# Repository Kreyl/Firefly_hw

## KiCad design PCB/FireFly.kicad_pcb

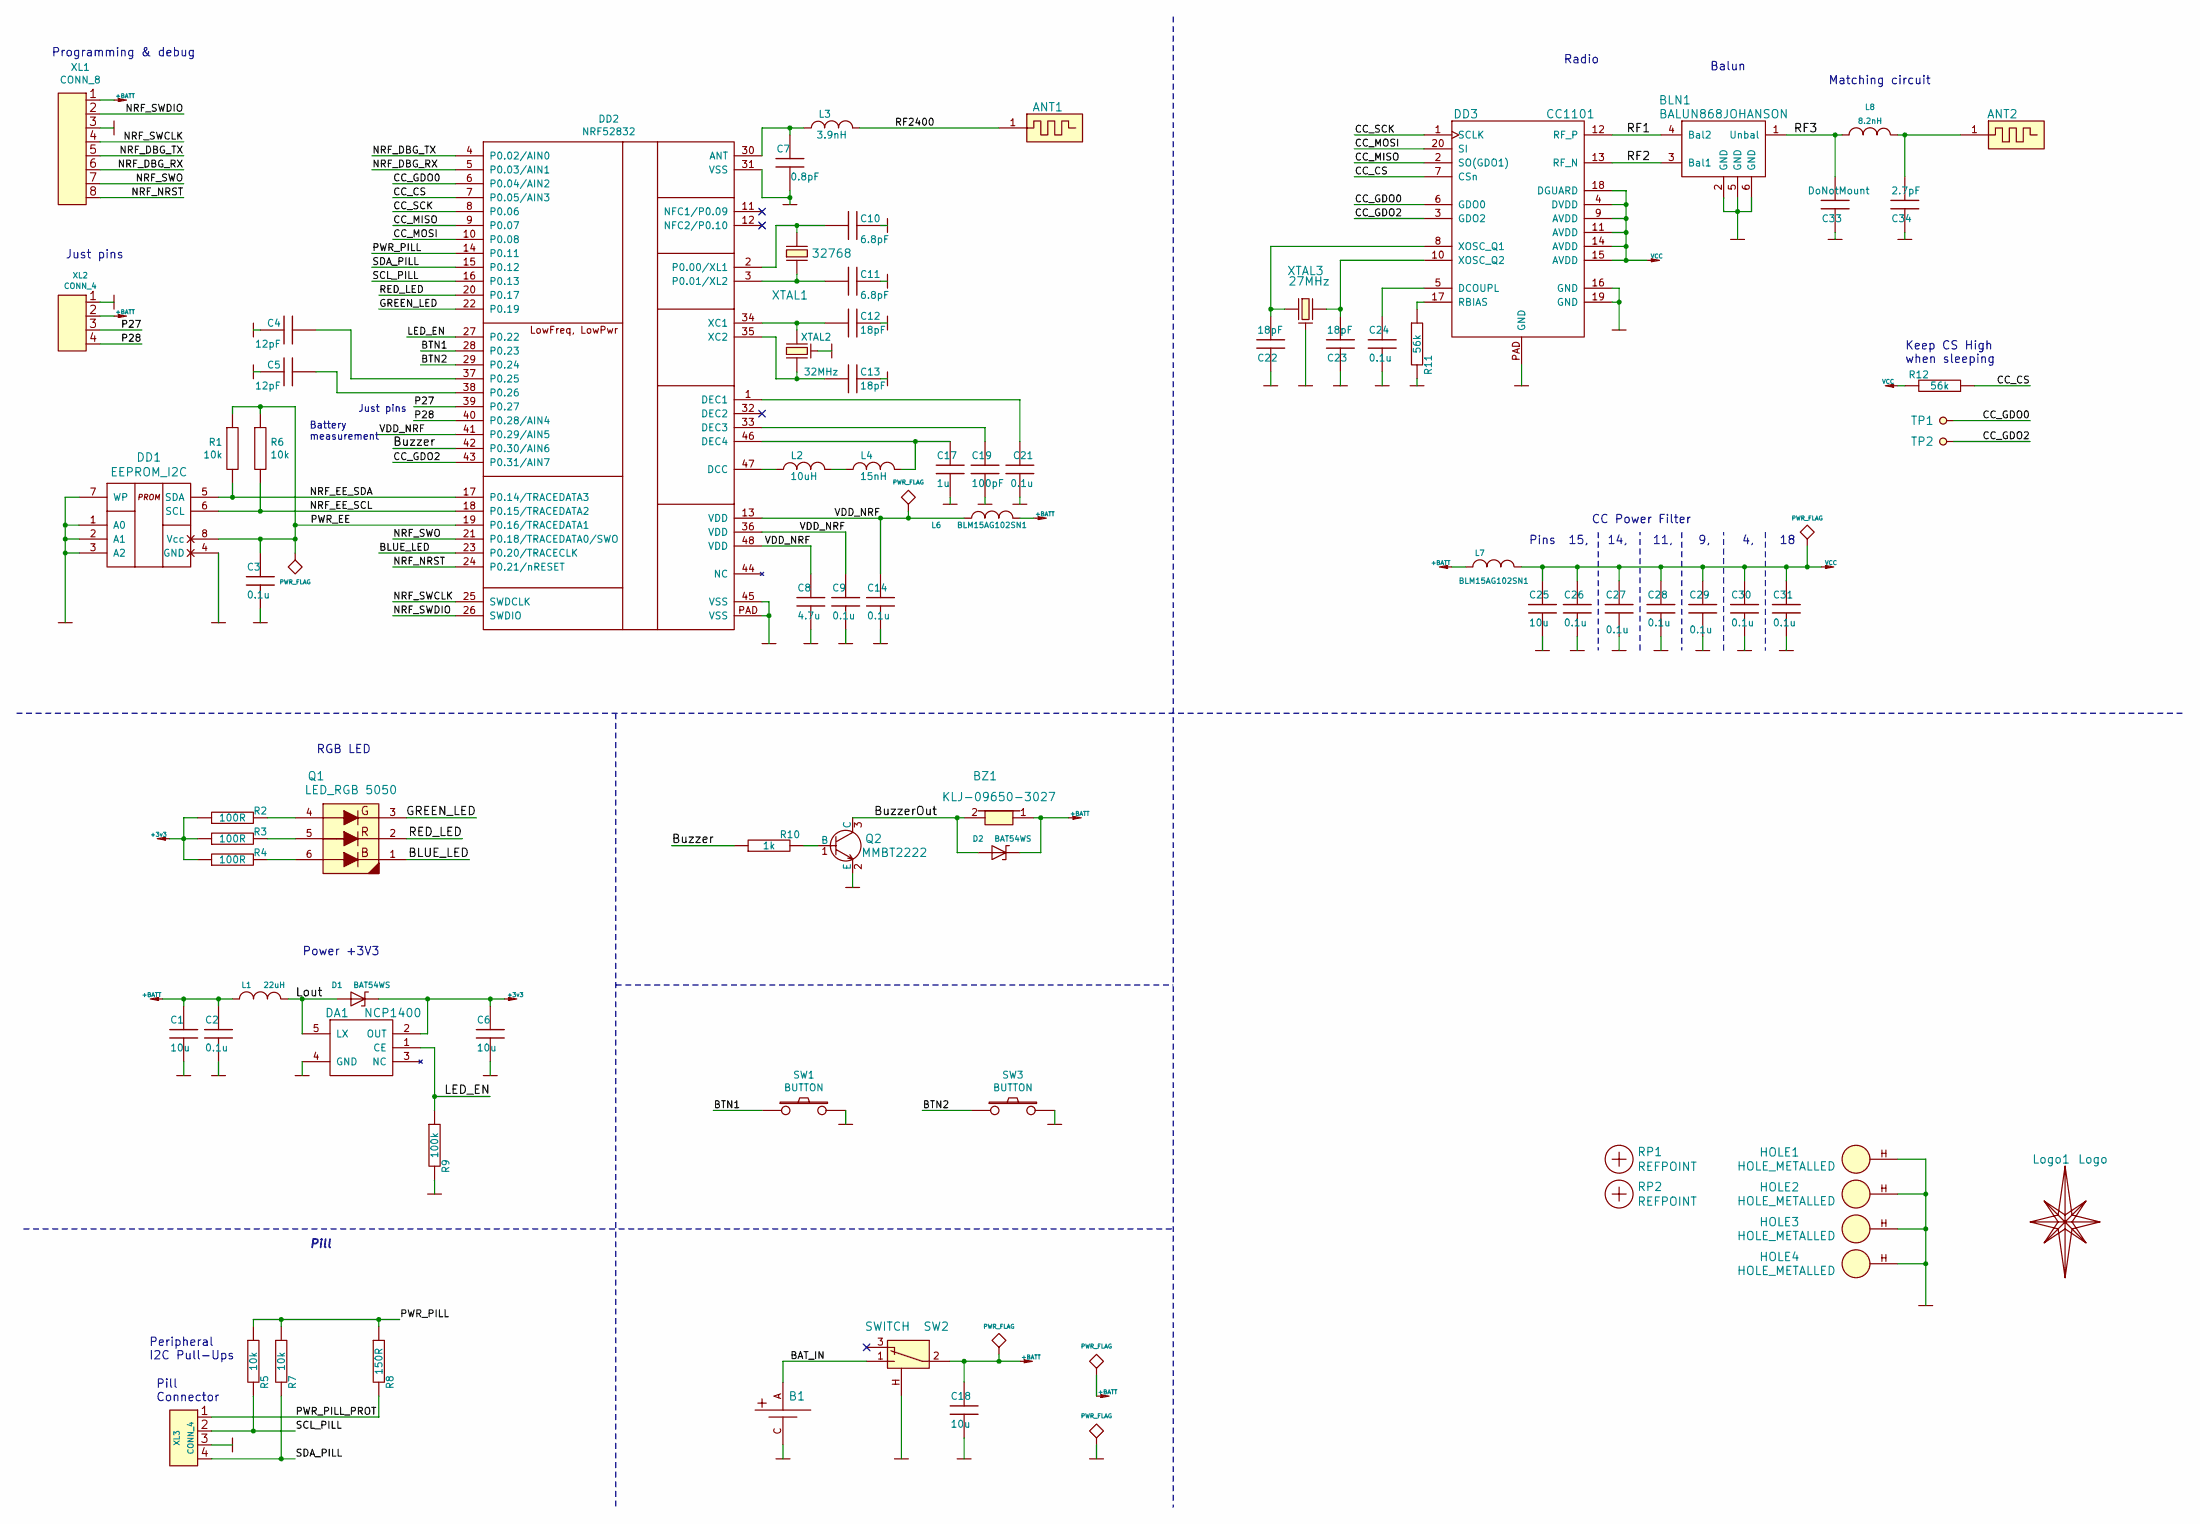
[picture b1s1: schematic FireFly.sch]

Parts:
ANT1: ANT_GENERAL; Firefly_2400
ANT2: ANT_PCB_MONO_2PIN; Firefly_868
B1: BAT_HOLDER; BATTERY_AAA_X2_PLUS_LEFT
BLN1: BALUN868JOHANSON; BALUN_JOHANSON868
BZ1: KLJ-09650-3027; BUZZER_KLJ-09650-3027
C1, C6, C18, C25: 10u; CAP_0603
C2, C3, C9, C14, C21, C24, C26, C27, C28, C29, C30, C31: 0.1u; CAP_0402
C4, C5: 12pF; CAP_0402
C7: 0.8pF; CAP_0402
C8: 4.7u; CAP_0603
C10, C11: 6.8pF; CAP_0402
C12, C13, C22, C23: 18pF; CAP_0402
C17: 1u; CAP_0402
C19: 100pF; CAP_0402
C33: DoNotMount; CAP_0402
C34: 2.7pF; CAP_0402
D1, D2: BAT54WS; SOD323
DA1: NCP1400; SOT23-5
DD1: EEPROM_I2C; SO8_150MIL
DD2: NRF52832; QFN-48_EP_6x6_Pitch0.4mm
DD3: CC1101; QFN20
HOLE1, HOLE2, HOLE3, HOLE4: HOLE_METALLED; Hole2d2_out3d5mm
L1: 22uH; IND_1210_LQH32C
L2: 10uH; IND_0603
L3: 3.9nH; IND_0402
L4: 15nH; IND_0402
L6, L7: BLM15AG102SN1; IND_0402
L8: 8.2nH; IND_0402
Logo1: Logo; Ostranna_12d7_10d1
Q1: LED_RGB 5050; LED_5050
Q2: MMBT2222; SOT23-3
R1, R5, R6, R7: 10k; RES_0603
R2, R3, R4: 100R; RES_0603
R8: 150R; RES_0603
R9: 100k; RES_0603
R10: 1k; RES_0603
R11, R12: 56k; RES_0603
RP1, RP2: REFPOINT; REF_POINT_1MM
SW1, SW3: BUTTON; BTN_4x4_SMD
SW2: SWITCH; SW_SS-1P2T_Housing
TP1, TP2: TESTPOINT; TESTPOINT_1MM
XL1: CONN_8; PLD-8_LOCK
XL2: CONN_4; PLS-4
XL3: CONN_4; PBS-4R
XTAL1: 32768; 03215C2
XTAL2: 32MHz; 03225C4
XTAL3: 27MHz; 03225C4

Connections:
+3v3: C6.2, D1.C, DA1.2 (OUT), R2.1, R3.1, R4.1
+BATT: BZ1.1, C1.2, C2.2, C18.2, D2.C, L1.2, L6.2, L7.2, SW2.2, XL1.1, XL2.2 (PM)
/BAT_IN: B1.A, SW2.1
/BLUE_LED: DD2.23 (P0.20/TRACECLK), Q1.1
/BTN1: DD2.28 (P0.23), SW1.1
/BTN2: DD2.29 (P0.24), SW3.1
/Buzzer: DD2.42 (P0.30/AIN6), R10.1
/BuzzerOut: BZ1.2, D2.A, Q2.3 (C)
/CC_CS: DD2.7 (P0.05/AIN3), DD3.7 (CSn), R12.1
/CC_GDO0: DD2.6 (P0.04/AIN2), DD3.6 (GDO0), TP1.1
/CC_GDO2: DD2.43 (P0.31/AIN7), DD3.3 (GDO2), TP2.1
/CC_MISO: DD2.9 (P0.07), DD3.2 (SO(GDO1))
/CC_MOSI: DD2.10 (P0.08), DD3.20 (SI)
/CC_SCK: DD2.8 (P0.06), DD3.1 (SCLK)
/GREEN_LED: DD2.22 (P0.19), Q1.3
/LED_EN: DA1.1 (CE), DD2.27 (P0.22), R9.1
/Lout: D1.A, DA1.5 (LX), L1.1
/NRF_DBG_RX: DD2.5 (P0.03/AIN1), XL1.6
/NRF_DBG_TX: DD2.4 (P0.02/AIN0), XL1.5
/NRF_EE_SCL: DD1.6 (SCL), DD2.18 (P0.15/TRACEDATA2), R6.2
/NRF_EE_SDA: DD1.5 (SDA), DD2.17 (P0.14/TRACEDATA3), R1.2
/NRF_NRST: DD2.24 (P0.21/nRESET), XL1.8
/NRF_SWCLK: DD2.25 (SWDCLK), XL1.4
/NRF_SWDIO: DD2.26 (SWDIO), XL1.2
/NRF_SWO: DD2.21 (P0.18/TRACEDATA0/SWO), XL1.7
/P27: DD2.39 (P0.27), XL2.3
/P28: DD2.40 (P0.28/AIN4), XL2.4
/PWR_EE: C3.2, DD1.8 (Vcc), DD2.19 (P0.16/TRACEDATA1), R1.1, R6.1
/PWR_PILL: DD2.14 (P0.11), R5.1, R7.1, R8.1
/PWR_PILL_PROT: R8.2, XL3.1
/RED_LED: DD2.20 (P0.17), Q1.2
/RF1: BLN1.4 (Bal2), DD3.12 (RF_P)
/RF2: BLN1.3 (Bal1), DD3.13 (RF_N)
/RF3: BLN1.1 (Unbal), C33.1, L8.2
/RF2400: ANT1.1, L3.2
/SCL_PILL: DD2.16 (P0.13), R5.2, XL3.2 (PM)
/SDA_PILL: DD2.15 (P0.12), R7.2, XL3.4
/VDD_NRF: C8.2, C9.2, C14.2, DD2.13 (VDD), DD2.36 (VDD), DD2.41 (P0.29/AIN5), DD2.48 (VDD), L6.1
GND: B1.C, BLN1.2 (GND), BLN1.5 (GND), BLN1.6 (GND), C1.1, C2.1, C3.1, C4.1, C5.1, C6.1, C7.1, C8.1, C9.1, C10.1, C11.1, C12.1, C13.1, C14.1, C17.1, C18.1, C19.1, C21.1, C22.2, C23.2, C24.1, C25.2, C26.2, C27.2, C28.2, C29.2, C30.2, C31.2, C33.2, C34.2, DA1.4 (GND), DD1.1 (A0), DD1.2 (A1), DD1.3 (A2), DD1.4 (GND), DD1.7 (WP), DD2.31 (VSS), DD2.45 (VSS), DD2.PAD (VSS), DD3.16 (GND), DD3.19 (GND), DD3.PAD (GND), HOLE1.H, HOLE2.H, HOLE3.H, HOLE4.H, Q2.2 (E), R9.2, R11.2, SW1.2, SW2.H, SW3.2, XL1.3, XL2.1, XL3.3, XTAL2.H, XTAL3.H
unnamed: ANT2.1, C34.1, L8.1
unnamed: C4.2, DD2.37 (P0.25)
unnamed: C5.2, DD2.38 (P0.26)
unnamed: C7.2, DD2.30 (ANT), L3.1
unnamed: C10.2, DD2.2 (P0.00/XL1), XTAL1.2
unnamed: C11.2, DD2.3 (P0.01/XL2), XTAL1.1
unnamed: C12.2, DD2.34 (XC1), XTAL2.2
unnamed: C13.2, DD2.35 (XC2), XTAL2.1
unnamed: C17.2, DD2.46 (DEC4), L4.2
unnamed: C19.2, DD2.33 (DEC3)
unnamed: C21.2, DD2.1 (DEC1)
unnamed: C22.1, DD3.8 (XOSC_Q1), XTAL3.1
unnamed: C23.1, DD3.10 (XOSC_Q2), XTAL3.2
unnamed: C24.2, DD3.5 (DCOUPL)
unnamed: DD2.47 (DCC), L2.1
unnamed: DD3.17 (RBIAS), R11.1
unnamed: L2.2, L4.1
unnamed: Q1.4 (B), R2.2
unnamed: Q1.5 (G), R3.2
unnamed: Q1.6, R4.2
unnamed: Q2.1 (B), R10.2
VCC: C25.1, C26.1, C27.1, C28.1, C29.1, C30.1, C31.1, DD3.4 (DVDD), DD3.9 (AVDD), DD3.11 (AVDD), DD3.14 (AVDD), DD3.15 (AVDD), DD3.18 (DGUARD), L7.1, R12.2

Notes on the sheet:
RGB LED
Power +3V3
CC Power Filter
Pins 15, 14, 11, 9, 4, 18
Programming & debug
Peripheral I2C Pull-Ups
Pill Connector
Pill
Radio
Matching circuit
Balun
Keep CS High when sleeping
Just pins
Battery measurement

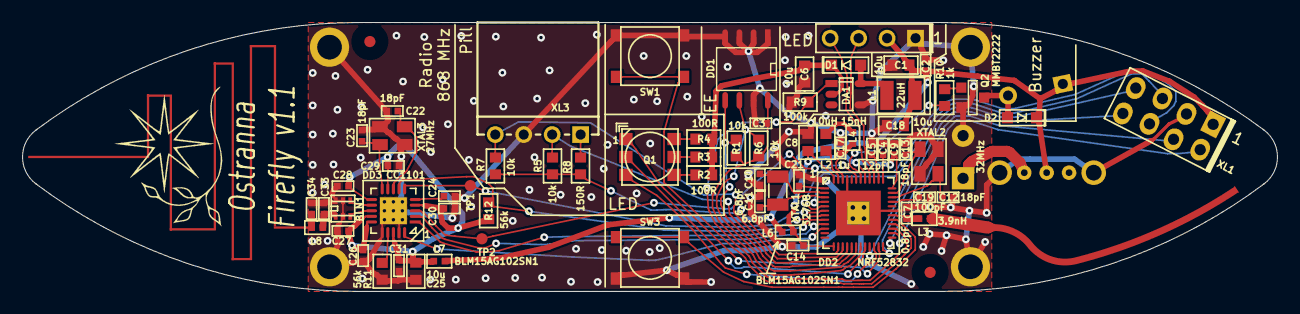
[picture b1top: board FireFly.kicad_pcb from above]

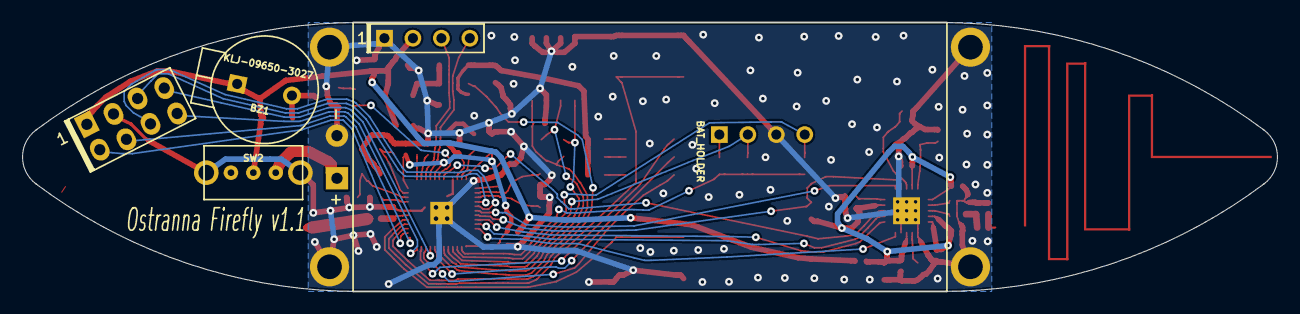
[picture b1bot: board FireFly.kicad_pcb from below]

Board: 2 copper layers, 112.0 x 24.0 mm, 80 parts (3 on the bottom side), 61 nets.

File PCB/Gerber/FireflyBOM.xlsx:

Ref | Value | Footprint | Datasheet | Manufacturer | Vendor | Comment
BLN1 | BALUN868JOHANSON | Radio:BALUN_JOHANSON868
BZ1 | PS-9627 | Installation:BUZZER_HC0903 |  |  |  | Предоставим
C1 | 10u | Capacitors:CAP_0603
C2 | 0.1u | Capacitors:CAP_0402
C3 | 0.1u | Capacitors:CAP_0402
C4 | 12pF | Capacitors:CAP_0402
C5 | 12pF | Capacitors:CAP_0402
C6 | 10u | Capacitors:CAP_0603
C7 | 0.8pF | Capacitors:CAP_0402
C8 | 4.7u | Capacitors:CAP_0603
C9 | 0.1u | Capacitors:CAP_0402
C10 | 6.8pF | Capacitors:CAP_0402
C11 | 6.8pF | Capacitors:CAP_0402
C12 | 18pF | Capacitors:CAP_0402
C13 | 18pF | Capacitors:CAP_0402
C14 | 0.1u | Capacitors:CAP_0402
C17 | 1u | Capacitors:CAP_0402
C18 | 10u | Capacitors:CAP_0603
C19 | 100pF | Capacitors:CAP_0402
C21 | 0.1u | Capacitors:CAP_0402
C22 | 18pF | Capacitors:CAP_0402
C23 | 18pF | Capacitors:CAP_0402
C24 | 0.1u | Capacitors:CAP_0402
C25 | 10u | Capacitors:CAP_0603
C26 | 0.1u | Capacitors:CAP_0402
C27 | 0.1u | Capacitors:CAP_0402
C28 | 0.1u | Capacitors:CAP_0402
C29 | 0.1u | Capacitors:CAP_0402
C30 | 0.1u | Capacitors:CAP_0402
C31 | 0.1u | Capacitors:CAP_0402
D1 | BAT54WS | Diodes:SOD323
DA1 | NCP1400 | SOT:SOT23-5
DD1 | M24C08-WMN6P | SO_DIL_TSSOP:SO8_150MIL
DD2 | NRF52832 | QFN_DFN:QFN-48_EP_6x6_Pitch0.4mm
DD3 | CC1101 | QFN_DFN:QFN20
L1 | 22uH | Inductors:IND_1210_LQH32C
L2 | 10uH | Inductors:IND_0603
L3 | 3.9nH | Inductors:IND_0402
L4 | 15nH | Inductors:IND_0402
L6 | BLM15AG102SN1 | Inductors:IND_0402
L7 | BLM15AG102SN1 | Inductors:IND_0402
Q1 | LED_RGB 5050 | LEDs:LED_5050 |  |  |  | Предоставим
Q2 | MMBT2222 | SOT:SOT23-3
R1 | 10k | Resistors:RES_0603
R2 | 100R | Resistors:RES_0603
R3 | 100R | Resistors:RES_0603
R4 | 100R | Resistors:RES_0603
R5 | 10k | Resistors:RES_0603
R6 | 10k | Resistors:RES_0603
R7 | 10k | Resistors:RES_0603
R8 | 150R | Resistors:RES_0603
R9 | 100k | Resistors:RES_0603
R10 | 1k | Resistors:RES_0603
R11 | 56k | Resistors:RES_0603
R12 | 56k | Resistors:RES_0603
SW1 | BUTTON | BtnsSwitches:BTN_4x4_SMD
SW2 | SWITCH | BtnsSwitches:SW_SS-1P2T_Housing |  |  |  | Предоставим
SW3 | BUTTON | BtnsSwitches:BTN_4x4_SMD
XL3 | CONN_4 | Connectors:PBS-4R |  |  |  | Предоставим
XTAL1 | 32768 | Quartz:03215C2
XTAL2 | 32MHz | Quartz:03225C4
XTAL3 | 27MHz | Quartz:03225C4 |  |  |  | Предоставим

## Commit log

2019-07-11 started
2019-07-11 Proceeding w sch
2019-07-11 Sch seems done
2019-07-12 pcb under construction
2019-07-22 v1 sent to factory
2019-09-01 Antenna matched
2019-12-18 Preparing for production
2019-12-18 PCB v1.1
